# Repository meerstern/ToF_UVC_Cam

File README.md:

# ToF UVC Camera Board

## Overview 
  * This is a ToF camera board equipped with the [AMS TMF8829 ToF sensor][1].  
  * Outputs 48x32 ToF data as a UVC webcam image.  
  * The microcontroller used is the RP2040.  
  * Source code using the Pico-SDK is available.
  * Measuring up to 1.4 m in high-resolution mode and up to 5.7 m in standard mode.

## Detailed Specifications
  * The USB port uses a Type-C connection.
  * The board is recognized as a UVC (USB Video Class) device with a resolution of 128x96.
  * The ToF resolution is 48x32 as a UVC webcam image.
  * It is displayed scaled up by a factor of two(96x64).
  * Measuring up to 1.4 m in high-resolution mode(SW3 SEN ON)
  * Measuring up to 5.7 m in standard mode(SW3 SEN OFF)
  * Switch the color scale between absolute(SW3 ABS ON) and relative modes(SW3 ABS OFF).
  * In the relative mode, the color scale is calculated based on the overall maximum and minimum values.
  * For absolute mode, the color scale is calculated based on a minimum of 0 and a maximum of 1.4 m in high-resolution mode, or 5.7 m in normal mode.
  * If horizontally flip the output image, please flash the `UVC_RP2040_XXXXXX_vXX_Mirror.uf2` file.
  * In the code, enable `MIRRR_OUTPUT_MODE` in `UVC_RP2040.h`.
  * If the confidence value is less than 10, it will be displayed in black. 
  * The frame rate depends on the conditions, but it is around 8 FPS.
  * 80° FOV, 1cm minimum distance and 0.25 mm resolution
  * Power 5V/0.2A from USB Type-C Port
  * The maximum range of 11m is supported only at 8x8 resolution; this board does not support it.
  * The board size is 40mm x50 mm, the hole size is M3x4, the hole pitch is 34mm x44mm.
  * The sensor area on the board becomes hot. Please be careful.   

## Laser eye safety
The TMF8829 is designed to meet the Class 1 laser safety limits including single faults in
compliance with IEC / EN 60825-1:2014, EN 60825-1:2014+A11:2021 and Class 1 consumer
laser product according to EN 50689:2021.

## Updating the firmware
  * Connect the device to a PC (or similar) via USB Type-C.
  * Then press the RST button while holding down the BOOT button.
  * The device will be recognized as a USB drive.  
  * You can update the firmware by copying the firmware file(*.uf2) to the recognized USB drive.

## Appearance and examples

[1]: https://ams-osram.com/ja/products/sensor-solutions/direct-time-of-flight-sensors-dtof/ams-tmf8829-48x32-multi-zone-time-of-flight-sensor

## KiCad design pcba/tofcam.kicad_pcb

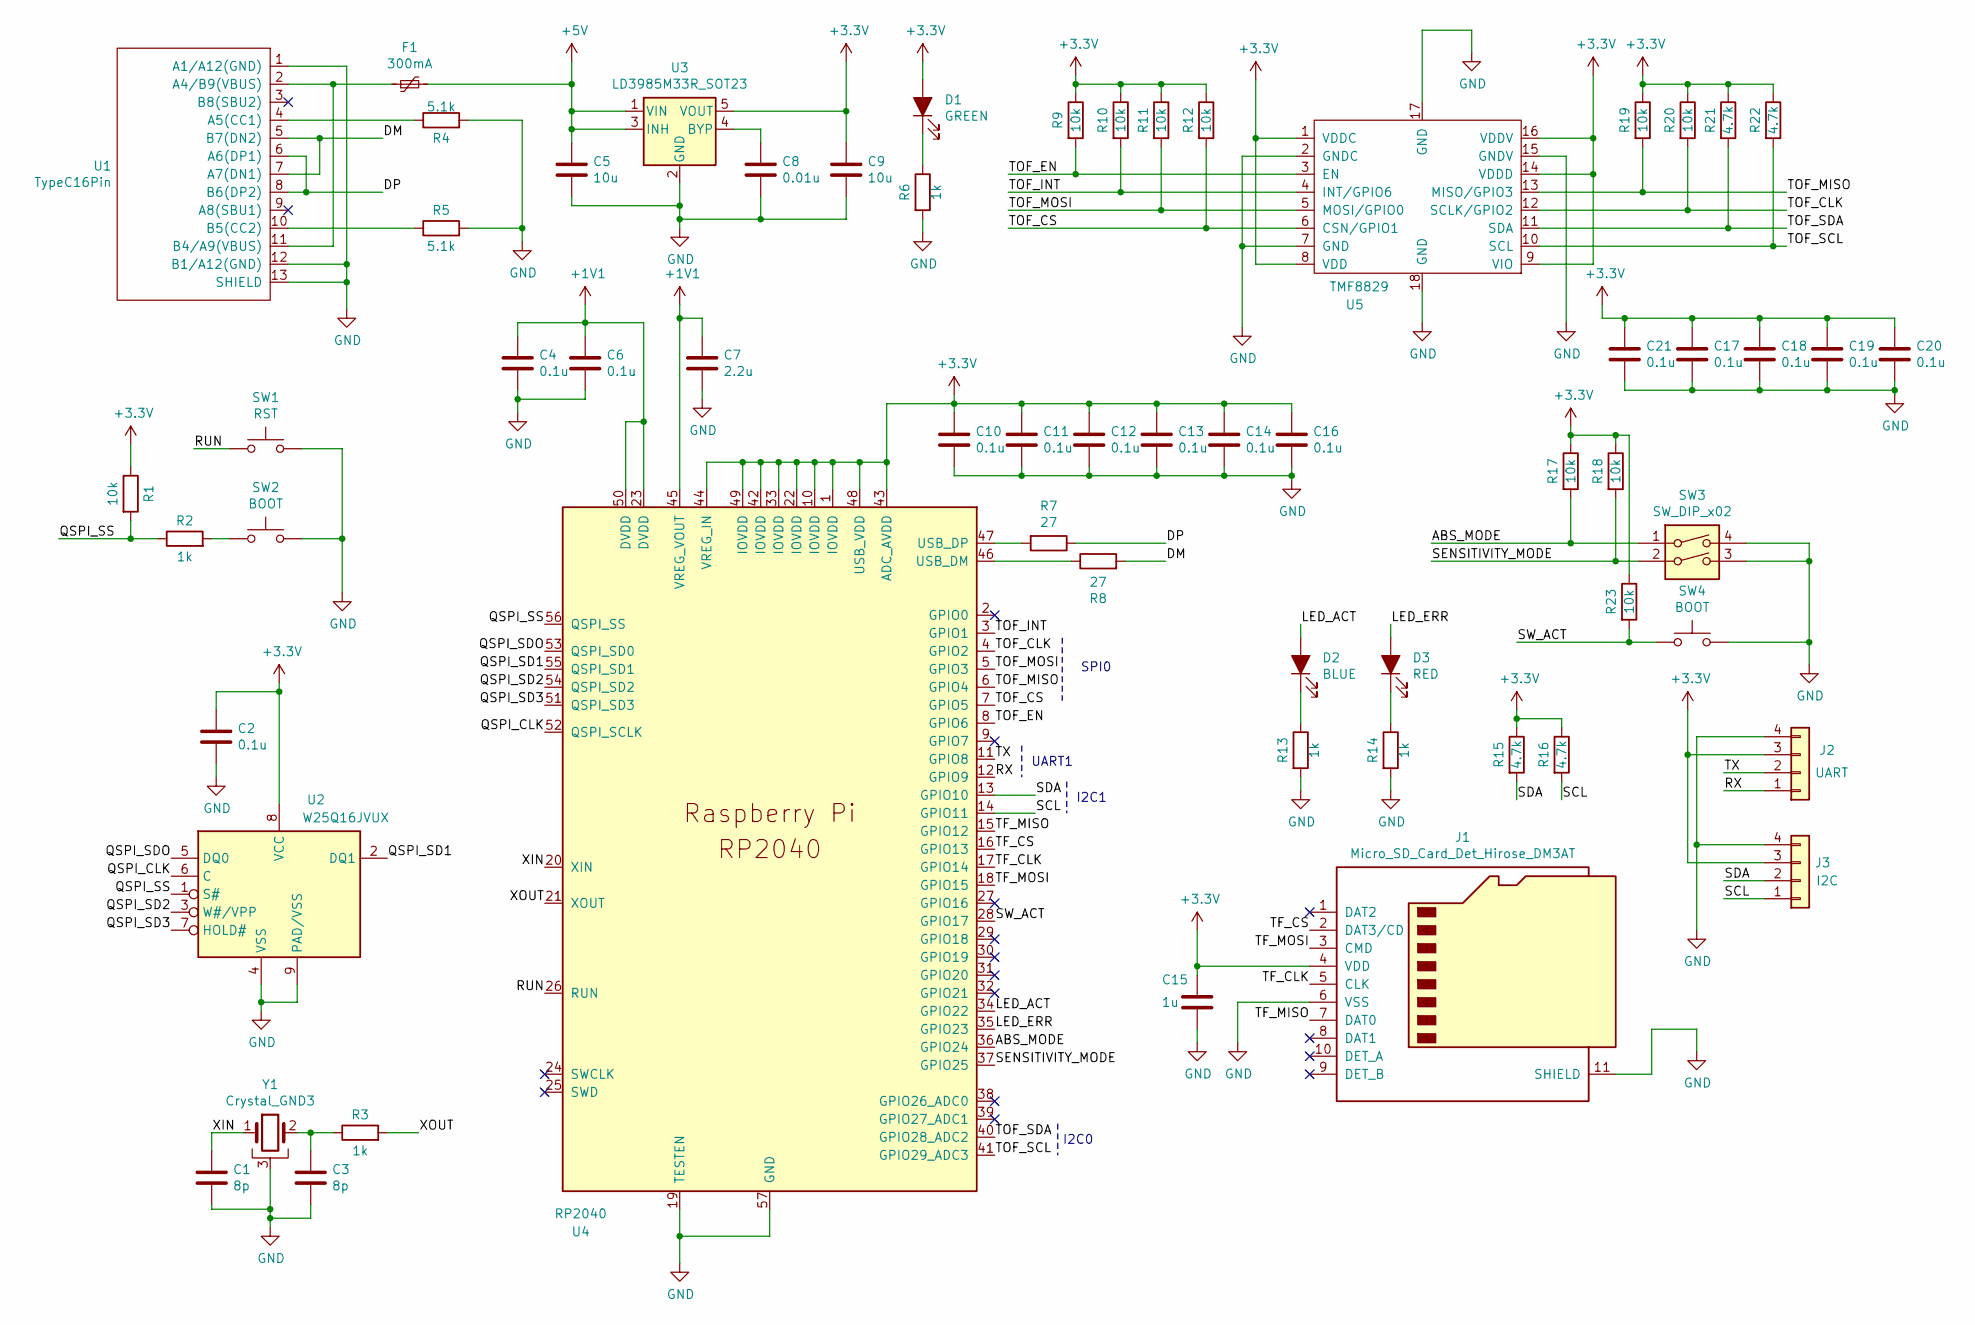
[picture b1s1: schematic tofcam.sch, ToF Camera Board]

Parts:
C1, C3: 8p; C_0603_1608Metric
C2, C4, C6, C10, C11, C12, C13, C14, C16, C17, C18, C19, C20, C21: 0.1u; C_0603_1608Metric
C5, C9: 10u; C_0805_2012Metric
C7: 2.2u; C_0603_1608Metric
C8: 0.01u; C_0603_1608Metric
C15: 1u; C_0603_1608Metric
D1: GREEN; LED_0603_1608Metric
D2: BLUE; LED_0603_1608Metric
D3: RED; LED_0603_1608Metric
F1: 300mA; Fuse_0603_1608Metric
J1: Micro_SD_Card_Det_Hirose_DM3AT; microSD_HC_Hirose_DM3AT-SF-PEJM5
J2: UART; GROVE
J3: I2C; GROVE
R1, R9, R10, R11, R12, R17, R18, R19, R20, R23: 10k; R_0603_1608Metric
R2, R3, R6, R13, R14: 1k; R_0603_1608Metric
R4, R5: 5.1k; R_0603_1608Metric
R7, R8: 27; R_0603_1608Metric
R15, R16, R21, R22: 4.7k; R_0603_1608Metric
SW1: RST; SKRPACE010
SW2, SW4: BOOT; SKRPACE010
SW3: SW_DIP_x02; SW_DIP_SPSTx02_Slide_Copal_CHS-02B_W7.62mm_P1.27mm
U1: TypeC16Pin; TypeC_16Pin
U2: W25Q16JVUX; SON-8-1EP_3x2mm_P0.5mm_EP1.4x1.6mm
U3: LD3985M33R_SOT23; SOT-23-5
U4: RP2040; RP2040-QFN-56
U5: TMF8829
Y1: Crystal_GND3; FA238V

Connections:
+1V1: C4.1, C6.1, C7.1, U4.23 (DVDD), U4.45 (VREG_VOUT), U4.50 (DVDD)
+3V3: C2.1, C9.1, C10.1, C11.1, C12.1, C13.1, C14.1, C15.1, C16.1, C17.1, C18.1, C19.1, C20.1, C21.1, D1.2 (A), J1.4 (VDD), J2.3, J3.3, R1.1, R9.1, R10.1, R11.1, R12.1, R15.1, R16.1, R17.1, R18.1, R19.1, R20.1, R21.1, R22.1, R23.1, U2.8 (VCC), U3.5 (VOUT), U4.1 (IOVDD), U4.10 (IOVDD), U4.22 (IOVDD), U4.33 (IOVDD), U4.42 (IOVDD), U4.43 (ADC_AVDD), U4.44 (VREG_IN), U4.48 (USB_VDD), U4.49 (IOVDD), U5.1 (VDDC), U5.8 (VDD), U5.9 (VIO), U5.14 (VDDD), U5.16 (VDDV)
+5V: C5.1, F1.2, U3.1 (VIN), U3.3 (INH)
/ABS_MODE: R17.2, SW3.1, U4.36 (GPIO24)
/DM: R8.2, U1.5 (B7(DN2)), U1.7 (A7(DN1))
/DP: R7.1, U1.6 (A6(DP1)), U1.8 (B6(DP2))
/LED_ACT: D2.2 (A), U4.34 (GPIO22)
/LED_ERR: D3.2 (A), U4.35 (GPIO23)
/QSPI_CLK: U2.6 (C), U4.52 (QSPI_SCLK)
/QSPI_SD1: U2.2 (DQ1), U4.55 (QSPI_SD1)
/QSPI_SD2: U2.3 (W#/VPP), U4.54 (QSPI_SD2)
/QSPI_SD3: U2.7 (HOLD#), U4.51 (QSPI_SD3)
/QSPI_SDO: U2.5 (DQ0), U4.53 (QSPI_SD0)
/QSPI_SS: R1.2, R2.1, U2.1 (S#), U4.56 (QSPI_SS)
/RUN: SW1.1, U4.26 (RUN)
/RX: J2.1, U4.12 (GPIO9)
/SCL: J3.1, R16.2, U4.14 (GPIO11)
/SDA: J3.2, R15.2, U4.13 (GPIO10)
/SENSITIVITY_MODE: R18.2, SW3.2, U4.37 (GPIO25)
/SW_ACT: R23.2, SW4.1, U4.28 (GPIO17)
/TF_CLK: J1.5 (CLK), U4.17 (GPIO14)
/TF_CS: J1.2 (DAT3/CD), U4.16 (GPIO13)
/TF_MISO: J1.7 (DAT0), U4.15 (GPIO12)
/TF_MOSI: J1.3 (CMD), U4.18 (GPIO15)
/TOF_CLK: R20.2, U4.4 (GPIO2), U5.12 (SCLK/GPIO2)
/TOF_CS: R12.2, U4.7 (GPIO5), U5.6 (CSN/GPIO1)
/TOF_EN: R9.2, U4.8 (GPIO6), U5.3 (EN)
/TOF_INT: R10.2, U4.3 (GPIO1), U5.4 (INT/GPIO6)
/TOF_MISO: R19.2, U4.6 (GPIO4), U5.13 (MISO/GPIO3)
/TOF_MOSI: R11.2, U4.5 (GPIO3), U5.5 (MOSI/GPIO0)
/TOF_SCL: R22.2, U4.41 (GPIO29_ADC3), U5.10 (SCL)
/TOF_SDA: R21.2, U4.40 (GPIO28_ADC2), U5.11 (SDA)
/TX: J2.2, U4.11 (GPIO8)
/XIN: C1.1, U4.20 (XIN), Y1.1
/XOUT: R3.2, U4.21 (XOUT)
GND: C1.2, C2.2, C3.2, C4.2, C5.2, C6.2, C7.2, C8.2, C9.2, C10.2, C11.2, C12.2, C13.2, C14.2, C15.2, C16.2, C17.2, C18.2, C19.2, C20.2, C21.2, J1.6 (VSS), J1.11 (SHIELD), J2.4, J3.4, R4.2, R5.2, R6.2, R13.2, R14.2, SW1.2, SW2.2, SW3.3, SW3.4, SW4.2, U1.1 (A1/A12(GND)), U1.12 (B1/A12(GND)), U1.13 (SHIELD), U2.4 (VSS), U2.9 (PAD/VSS), U3.2 (GND), U4.19 (TESTEN), U4.57 (GND), U5.2 (GNDC), U5.7 (GND), U5.15 (GNDV), U5.17 (GND), U5.18 (GND), Y1.3
unnamed: C3.1, R3.1, Y1.2
unnamed: C8.1, U3.4 (BYP)
unnamed: D1.1 (K), R6.1
unnamed: D2.1 (K), R13.1
unnamed: D3.1 (K), R14.1
unnamed: F1.1, U1.2 (A4/B9(VBUS)), U1.11 (B4/A9(VBUS))
unnamed: R2.2, SW2.1
unnamed: R4.1, U1.4 (A5(CC1))
unnamed: R5.1, U1.10 (B5(CC2))
unnamed: R7.2, U4.47 (USB_DP)
unnamed: R8.1, U4.46 (USB_DM)

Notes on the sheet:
I2C0
SPI0
UART1
I2C1

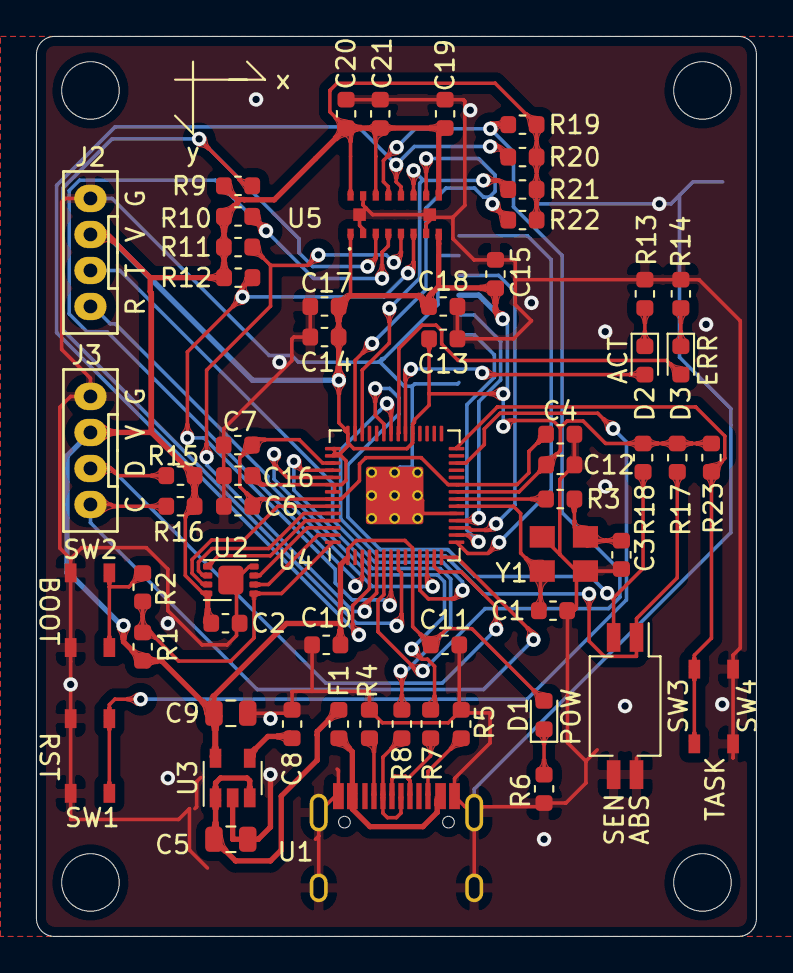
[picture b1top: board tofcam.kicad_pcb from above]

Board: 2 copper layers, 40.0 x 50.0 mm, 65 parts (1 on the bottom side), 47 nets.

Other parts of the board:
REF1, REF2, REF3, REF4: MountingHole_3.2mm_M3

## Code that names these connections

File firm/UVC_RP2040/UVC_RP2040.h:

#ifndef UVC_RP2040_H
#define UVC_RP2040_H
#include <stdbool.h>

/* UGUI Settings */
#define START_X_POS     14
#define START_Y_POS     12
#define CELL_SIZE       2
#define TOF_PIX_WIDTH   48
#define TOF_PIX_HEIGHT  32
#define TOF_PIX_BYTES   3   //Confidence 1byte, Distance 2byte
#define TMF8829_CONF_TH 30

#define TMF8829_BIT2MM  (0.25f)

//#define MIRRR_OUTPUT_MODE   1
#define TOF_HEADER_VERSION  "ToF CAM v1.2"

/* Communication Settings */

#define F(x) x

// SPI Defines
// We are going to use SPI 0, and allocate it to the following GPIO pins
// Pins can be changed, see the GPIO function select table in the datasheet for information on GPIO assignments
#define SPI_PORT spi0
#define PIN_MISO 4//16
#define PIN_CS   5//17
#define PIN_SCK  2//18
#define PIN_MOSI 3//19

// I2C defines
// This example will use I2C0 on GPIO8 (SDA) and GPIO9 (SCL) running at 400KHz.
// Pins can be changed, see the GPIO function select table in the datasheet for information on GPIO assignments
#define I2C_PORT i2c0
#define I2C_SDA 28//8
#define I2C_SCL 29//9

#define LED_ACT 22
#define LED_ERR 23   

#define SW_MODE_ABS 24
#define SW_MODE_SEN 25
#define SW_ACT      17  //For Future Use

#define I2C_CLK_SPEED               400000
#define UART_BAUD_RATE              115200


#define NORMAL_MAX_RANGE            (5700.0f)//mm
#define HIGH_ACC_MAX_RANGE          (1400.0f)//mm

extern volatile uint8_t     tofBuff[TOF_PIX_WIDTH*TOF_PIX_HEIGHT*TOF_PIX_BYTES];
extern volatile uint16_t    tofBuffIndex;
extern volatile bool        hasTofData;
extern volatile uint8_t     tofIndex;
#endif
